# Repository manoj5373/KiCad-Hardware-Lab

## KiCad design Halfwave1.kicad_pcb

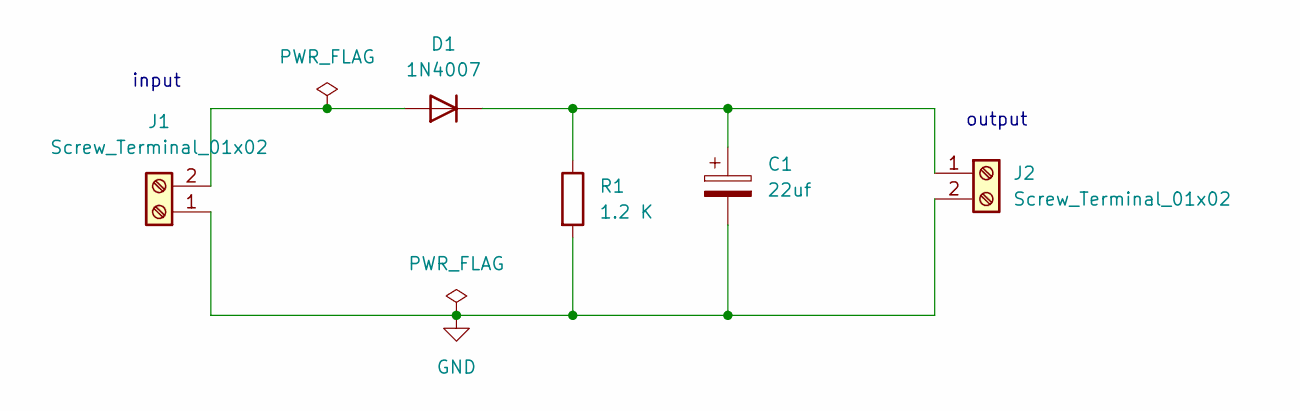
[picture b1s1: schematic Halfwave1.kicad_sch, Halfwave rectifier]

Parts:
C1: 22uf; CP_Radial_D5.0mm_P2.50mm
D1: 1N4007; D_DO-41_SOD81_P10.16mm_Horizontal
J1, J2: Screw_Terminal_01x02; TerminalBlock_Phoenix_PT-1,5-2-5.0-H_1x02_P5.00mm_Horizontal
R1: 1.2 K; R_Axial_DIN0207_L6.3mm_D2.5mm_P10.16mm_Horizontal

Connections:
GND: C1.2, J1.1, J2.2, R1.2
unnamed: D1.2 (A), J1.2
unnamed: C1.1, D1.1 (K), J2.1, R1.1

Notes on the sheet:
input
output

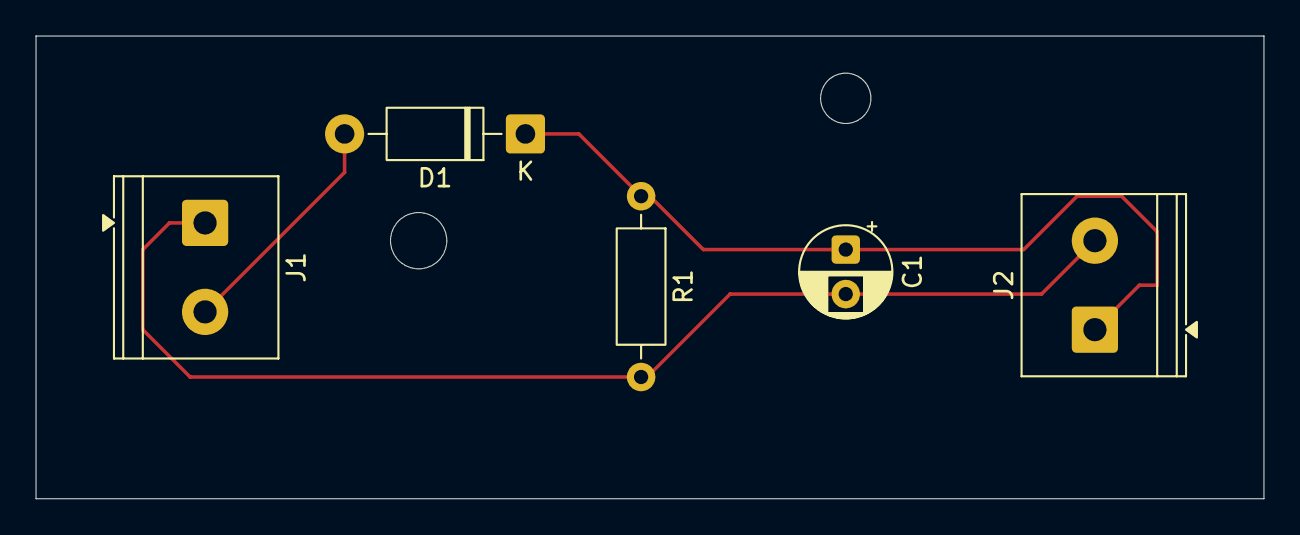
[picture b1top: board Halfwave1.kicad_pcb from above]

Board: 2 copper layers, 69.0 x 26.0 mm, 5 parts (0 on the bottom side), 3 nets.
